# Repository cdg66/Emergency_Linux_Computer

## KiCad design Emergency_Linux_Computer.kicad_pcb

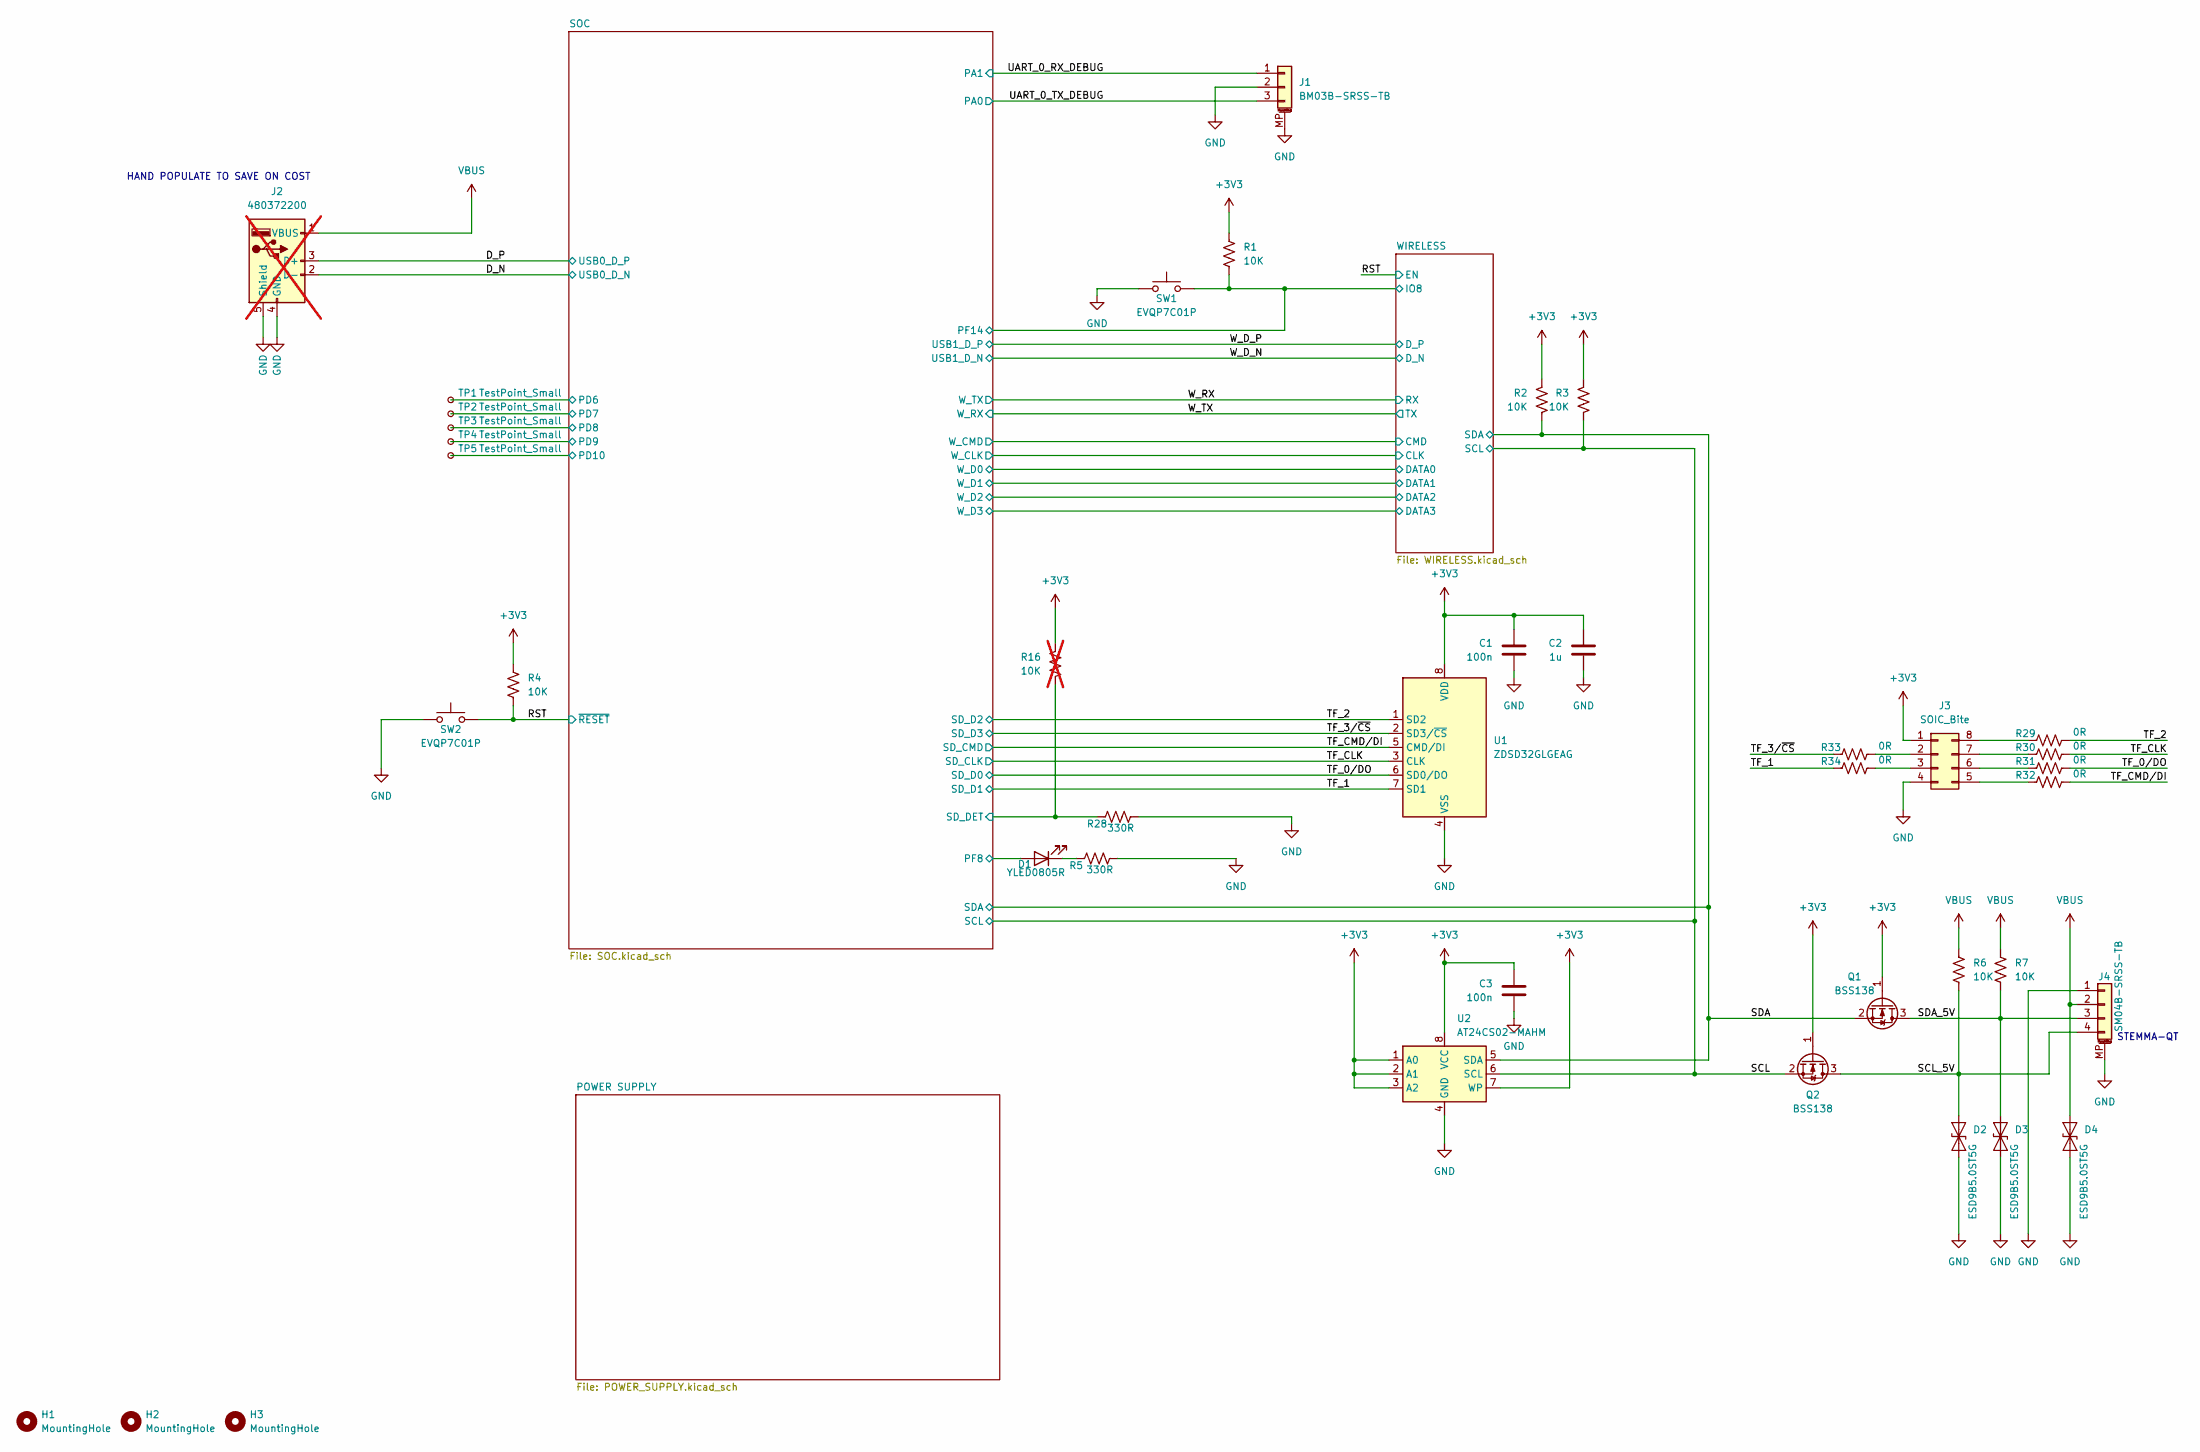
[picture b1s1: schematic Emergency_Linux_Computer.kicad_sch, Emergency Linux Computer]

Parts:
C1, C3: 100n; C_0201_0603Metric
C2: 1u; C_0603_1608Metric
D1: YLED0805R; LED_0805_2012Metric
D2, D3, D4: ESD9B5.0ST5G; D_SOD-923
H1, H2, H3: MountingHole; MountingHole_2.2mm_M2
J1: BM03B-SRSS-TB; JST_SH_BM03B-SRSS-TB_1x03-1MP_P1.00mm_Vertical
J2: 480372200; USB_A_Molex_48037-2200_Horizontal; not fitted
J3: SOIC_Bite; SOIC_clipProgSmall
J4: SM04B-SRSS-TB; JST_SH_SM04B-SRSS-TB_1x04-1MP_P1.00mm_Horizontal
Q1, Q2: BSS138; SOT-23
R1, R2, R3, R4, R6, R7: 10K; R_0201_0603Metric
R5, R28: 330R; R_0805_2012Metric
R16: 10K; R_0805_2012Metric; not fitted
R29, R30, R31, R32, R33, R34: 0R; R_0201_0603Metric
SW1, SW2: EVQP7C01P; SW_SPST_EVQP7C
TP1, TP2, TP3, TP4, TP5: TestPoint_Small; TestPoint_Pad_D1.0mm
U1: ZDSD32GLGEAG; LGA-8_8x6mm_P1.27mm
U2: AT24CS02-MAHM; DFN-8-1EP_3x2mm_P0.5mm_EP1.3x1.5mm

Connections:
+3V3: C1.1, C2.1, C3.1, J3.1, Q1.1 (G), Q2.1 (G), R1.1, R2.1, R3.1, R4.1, R16.1, U1.8 (VDD), U2.1 (A0), U2.2 (A1), U2.3 (A2), U2.7 (WP), U2.8 (VCC); also elsewhere on the board
/D_N: J2.2 (D-); also elsewhere on the board
/D_P: J2.3 (D+); also elsewhere on the board
/PF8: D1.2 (A)
/RST: R4.2, SW2.2; also elsewhere on the board
/SCL: Q2.2 (S), R3.2, U2.6 (SCL); also elsewhere on the board
/SCL_5V: D2.1 (A1), J4.4, Q2.3 (D), R6.2
/SDA: Q1.2 (S), R2.2, U2.5 (SDA); also elsewhere on the board
/SDA_5V: D3.1 (A1), J4.3, Q1.3 (D), R7.2
/SOC/PD6: TP1.1; also elsewhere on the board
/SOC/PD7: TP2.1; also elsewhere on the board
/SOC/PD8: TP3.1; also elsewhere on the board
/SOC/PD9: TP4.1; also elsewhere on the board
/SOC/PD10: TP5.1; also elsewhere on the board
/SOC/SD_DET: R16.2, R28.1; also elsewhere on the board
/TF_0/DO: R31.2, U1.6 (SD0/DO); also elsewhere on the board
/TF_1: R34.1, U1.7 (SD1); also elsewhere on the board
/TF_2: R29.2, U1.1 (SD2); also elsewhere on the board
/TF_3/~CS: R33.1, U1.2 (SD3/~CS); also elsewhere on the board
/TF_CLK: R30.2, U1.3 (CLK); also elsewhere on the board
/TF_CMD/DI: R32.2, U1.5 (CMD/DI); also elsewhere on the board
/UART_0_RX_DEBUG: J1.1; also elsewhere on the board
/UART_0_TX_DEBUG: J1.3; also elsewhere on the board
/WIRELESS/IO8: R1.2, SW1.2; also elsewhere on the board
GND: C1.2, C2.2, C3.2, D2.2 (A2), D3.2 (A2), D4.2 (A2), J1.2, J1.MP (MountPin), J2.4 (GND), J2.5 (Shield), J3.4, J4.1, J4.MP (MountPin), R5.2, R28.2, SW1.1, SW2.1, U1.4 (VSS), U2.4 (GND), U2.9 (GND); also elsewhere on the board
unnamed: D1.1 (K), R5.1
unnamed: J3.2, R33.2
unnamed: J3.3, R34.2
unnamed: J3.5, R32.1
unnamed: J3.6, R31.1
unnamed: J3.7, R30.1
unnamed: J3.8, R29.1
VBUS: D4.1 (A1), J2.1 (VBUS), J4.2, R6.1, R7.1; also elsewhere on the board

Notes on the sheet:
STEMMA-QT
HAND POPULATE TO SAVE ON COST

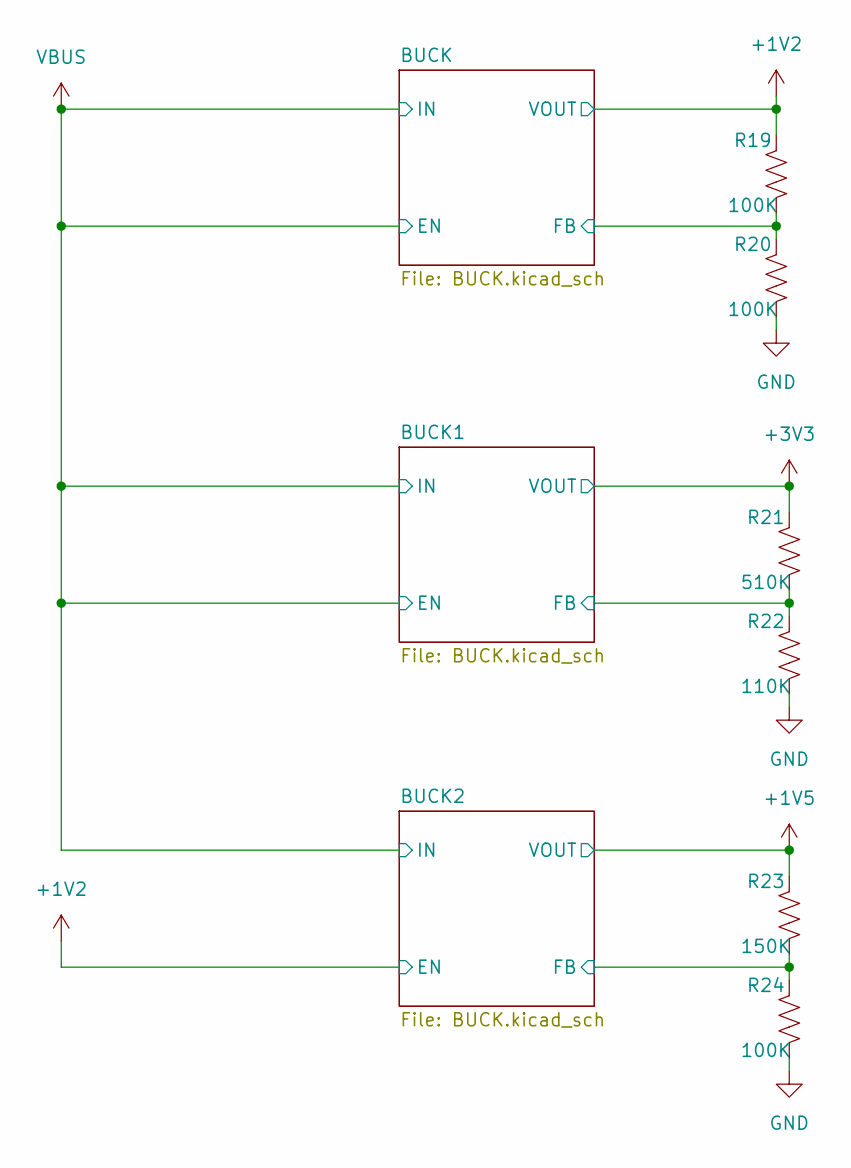
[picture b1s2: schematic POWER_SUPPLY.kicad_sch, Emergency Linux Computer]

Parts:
R19, R20, R24: 100K; R_0201_0603Metric
R21: 510K; R_0201_0603Metric
R22: 110K; R_0201_0603Metric
R23: 150K; R_0201_0603Metric

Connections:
+1V2: R19.1; also elsewhere on the board
+1V5: R23.1; also elsewhere on the board
+3V3: R21.1; also elsewhere on the board
/POWER SUPPLY/BUCK1/FB: R21.2, R22.1; also elsewhere on the board
/POWER SUPPLY/BUCK2/FB: R23.2, R24.1; also elsewhere on the board
/POWER SUPPLY/BUCK/FB: R19.2, R20.1; also elsewhere on the board
GND: R20.2, R22.2, R24.2; also elsewhere on the board

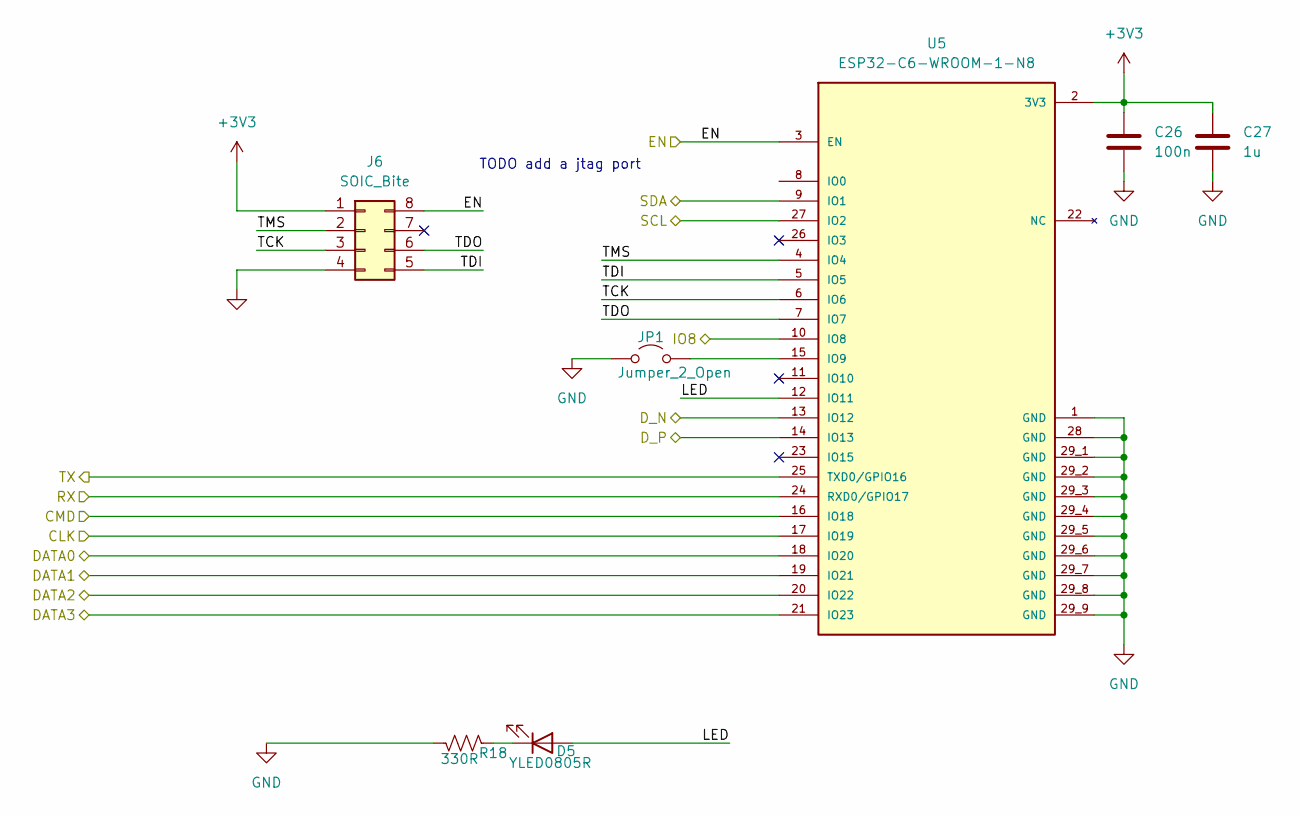
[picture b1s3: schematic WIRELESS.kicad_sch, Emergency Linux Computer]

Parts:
C26: 100n; C_0201_0603Metric
C27: 1u; C_0603_1608Metric
D5: YLED0805R; LED_0805_2012Metric
J6: SOIC_Bite; SOIC_clipProgSmall
JP1: Jumper_2_Open; SolderJumper-2_P1.3mm_Open_Pad1.0x1.5mm
R18: 330R; R_0805_2012Metric
U5: ESP32-C6-WROOM-1-N8; XCVR_ESP32-C6-WROOM-1-N8; PARTREV 1.0

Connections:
+3V3: C26.1, C27.1, J6.1, U5.2 (3V3); also elsewhere on the board
/RST: J6.8, U5.3 (EN); also elsewhere on the board
/SCL: U5.27 (IO2); also elsewhere on the board
/SDA: U5.9 (IO1); also elsewhere on the board
/SOC/W_CLK: U5.17 (IO19); also elsewhere on the board
/SOC/W_CMD: U5.16 (IO18); also elsewhere on the board
/SOC/W_D0: U5.18 (IO20); also elsewhere on the board
/SOC/W_D1: U5.19 (IO21); also elsewhere on the board
/SOC/W_D2: U5.20 (IO22); also elsewhere on the board
/SOC/W_D3: U5.21 (IO23); also elsewhere on the board
/WIRELESS/IO8: U5.10 (IO8); also elsewhere on the board
/WIRELESS/LED: D5.2 (A), U5.12 (IO11)
/WIRELESS/TCK: J6.3, U5.6 (IO6)
/WIRELESS/TDI: J6.5, U5.5 (IO5)
/WIRELESS/TDO: J6.6, U5.7 (IO7)
/WIRELESS/TMS: J6.2, U5.4 (IO4)
/W_D_N: U5.13 (IO12); also elsewhere on the board
/W_D_P: U5.14 (IO13); also elsewhere on the board
/W_RX: U5.24 (RXD0/GPIO17); also elsewhere on the board
/W_TX: U5.25 (TXD0/GPIO16); also elsewhere on the board
GND: C26.2, C27.2, J6.4, JP1.1 (A), R18.2, U5.1 (GND), U5.28 (GND), U5.29_1 (GND), U5.29_2 (GND), U5.29_3 (GND), U5.29_4 (GND), U5.29_5 (GND), U5.29_6 (GND), U5.29_7 (GND), U5.29_8 (GND), U5.29_9 (GND); also elsewhere on the board
unnamed: D5.1 (K), R18.1
unnamed: JP1.2 (B), U5.15 (IO9)

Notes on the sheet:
TODO add a jtag port

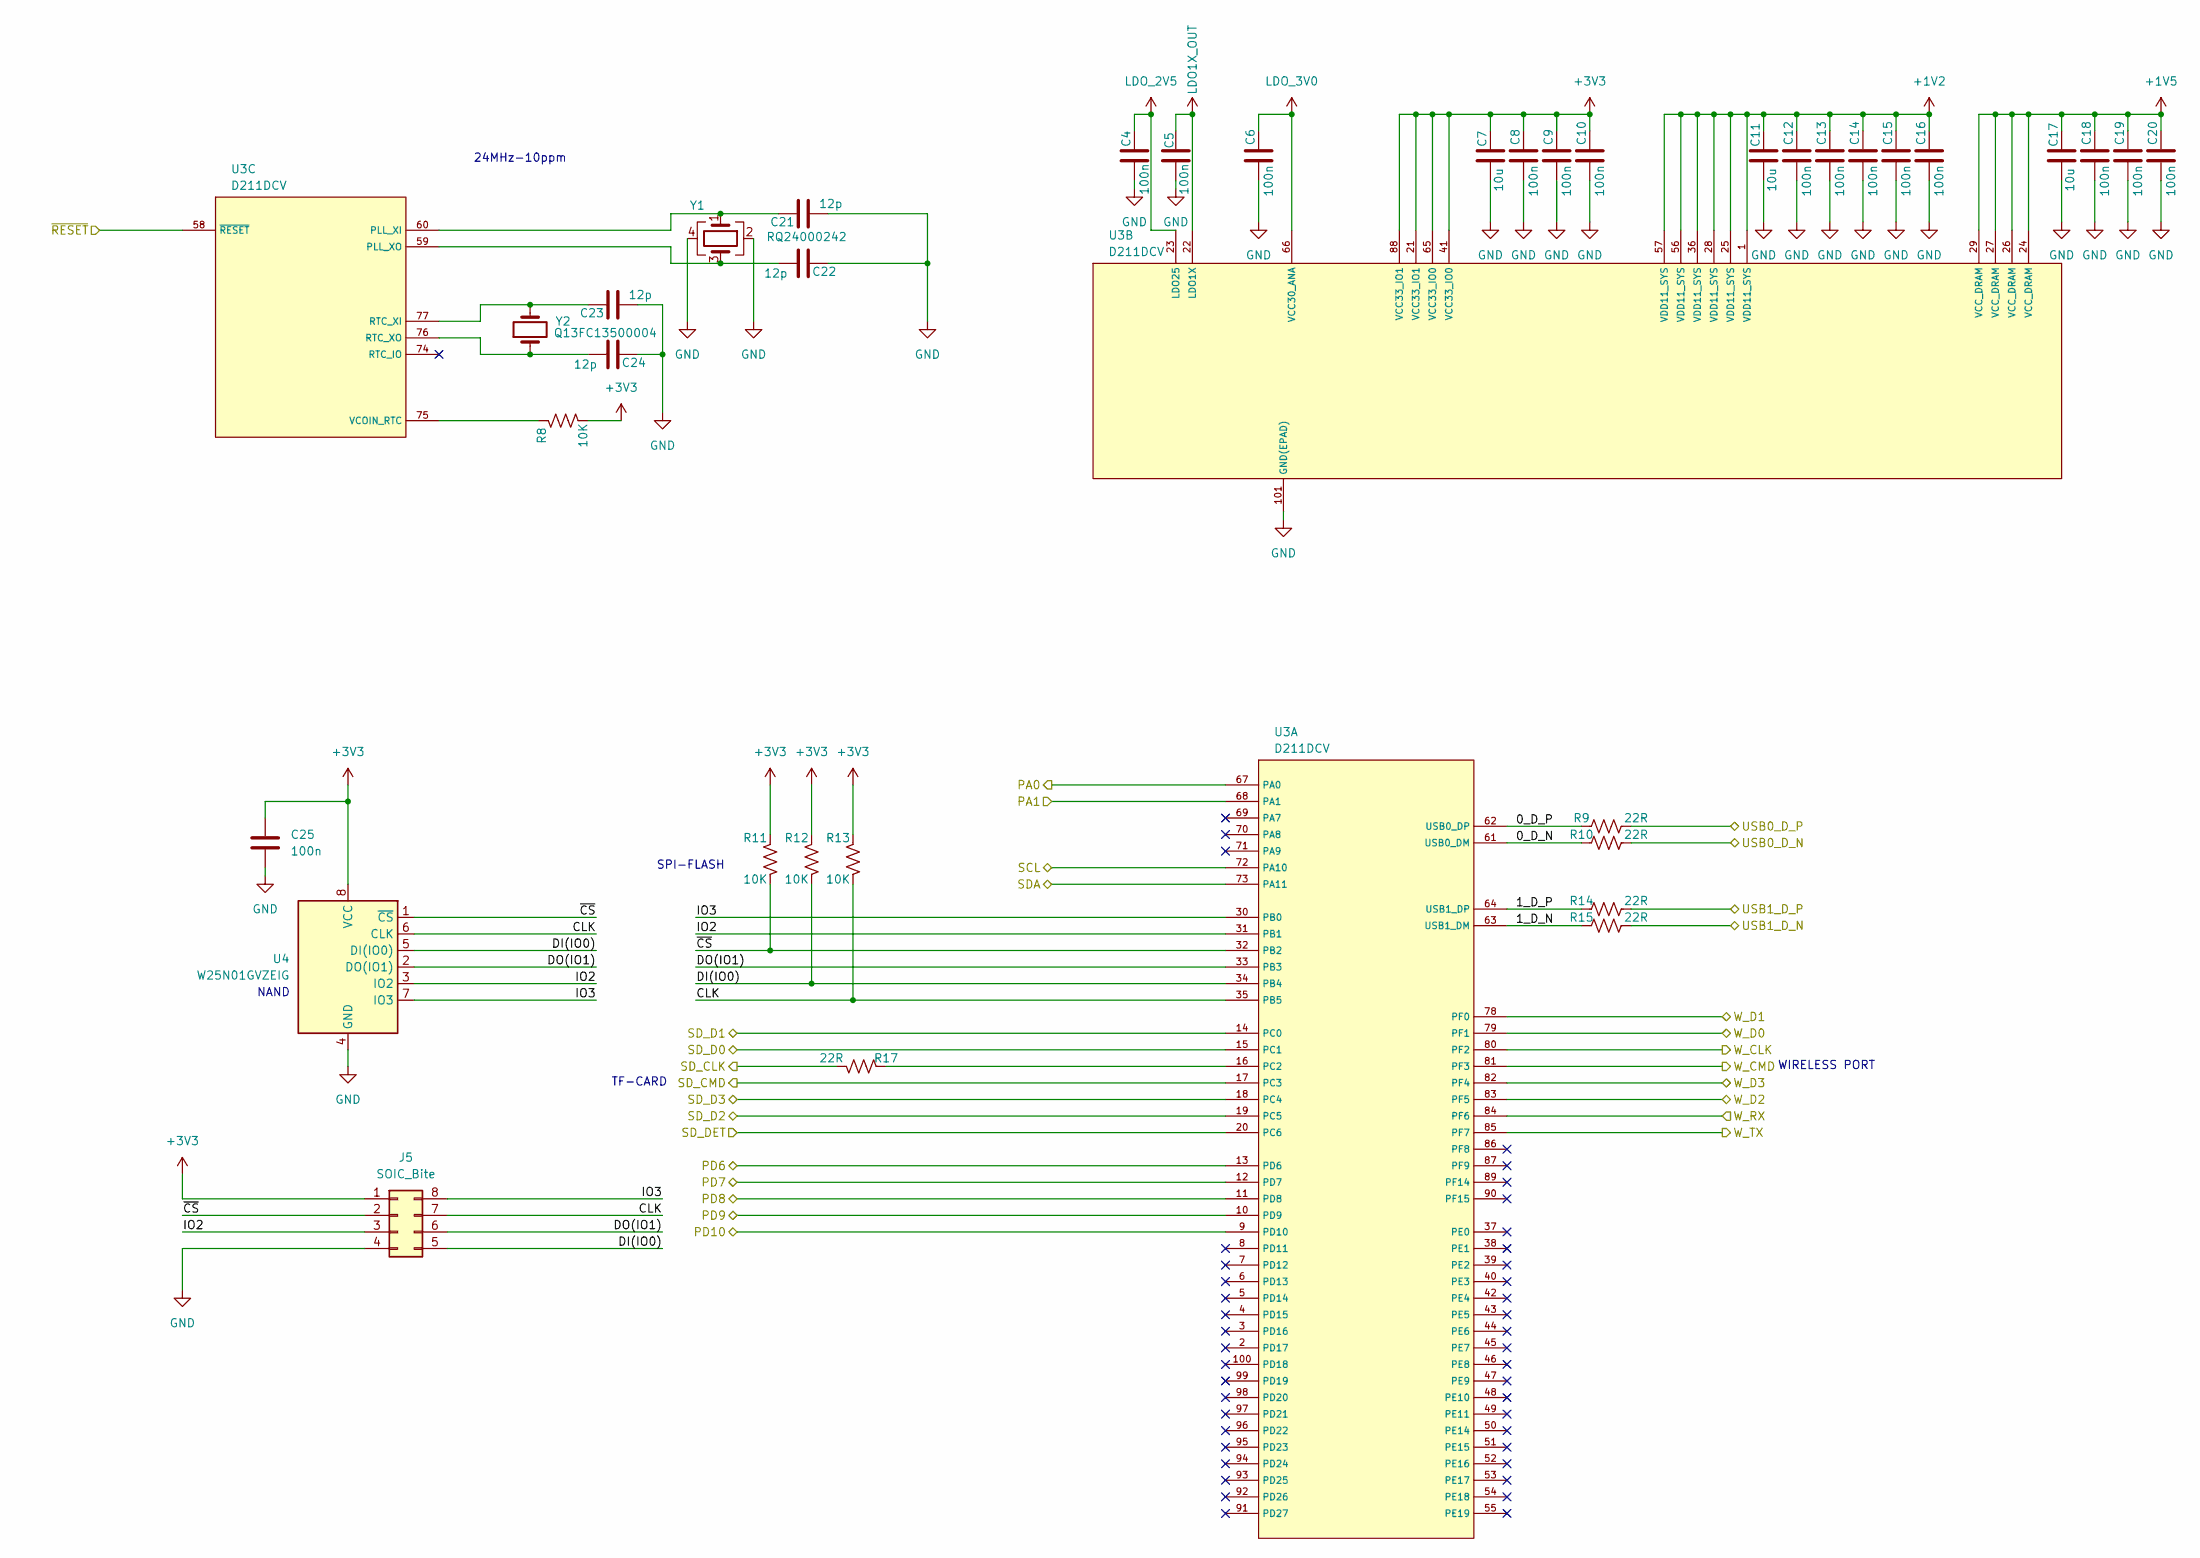
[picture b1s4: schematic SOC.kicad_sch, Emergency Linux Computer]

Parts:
C4, C5, C6, C8, C9, C10, C12, C13, C14, C15, C16, C18, C19, C20, C25: 100n; C_0201_0603Metric
C7, C11, C17: 10u; C_0603_1608Metric
C21, C22, C23, C24: 12p; C_0201_0603Metric
J5: SOIC_Bite; SOIC_clipProgSmall
R8, R11, R12, R13: 10K; R_0201_0603Metric
R9, R10, R14, R15, R17: 22R; R_0201_0603Metric
U3: D211DCV; ArtInChip_QFN-100-1EP_12x12mm_P0.4mm_EP7.4x7.4mm
U4: W25N01GVZEIG; WSON-8-1EP_8x6mm_P1.27mm_EP3.4x4.3mm
Y1: RQ24000242; Crystal_SMD_2520-4Pin_2.5x2.0mm
Y2: Q13FC13500004; Crystal_SMD_3215-2Pin_3.2x1.5mm

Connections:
+1V2: C11.1, C12.1, C13.1, C14.1, C15.1, C16.1, U3.1 (VDD11_SYS), U3.25 (VDD11_SYS), U3.28 (VDD11_SYS), U3.36 (VDD11_SYS), U3.56 (VDD11_SYS), U3.57 (VDD11_SYS); also elsewhere on the board
+1V5: C17.1, C18.1, C19.1, C20.1, U3.24 (VCC_DRAM), U3.26 (VCC_DRAM), U3.27 (VCC_DRAM), U3.29 (VCC_DRAM); also elsewhere on the board
+3V3: C7.1, C8.1, C9.1, C10.1, C25.1, J5.1, R8.2, R11.1, R12.1, R13.1, U3.21 (VCC33_IO1), U3.41 (VCC33_IO0), U3.65 (VCC33_IO0), U3.88 (VCC33_IO1), U4.8 (VCC); also elsewhere on the board
/D_N: R10.2; also elsewhere on the board
/D_P: R9.2; also elsewhere on the board
/RST: U3.58 (~RESET); also elsewhere on the board
/SCL: U3.72 (PA10); also elsewhere on the board
/SDA: U3.73 (PA11); also elsewhere on the board
/SOC/0_D_N: R10.1, U3.61 (USB0_DM)
/SOC/0_D_P: R9.1, U3.62 (USB0_DP)
/SOC/1_D_N: R15.1, U3.63 (USB1_DM)
/SOC/1_D_P: R14.1, U3.64 (USB1_DP)
/SOC/CLK: J5.7, R13.2, U3.35 (PB5), U4.6 (CLK)
/SOC/DI(IO0): J5.5, R12.2, U3.34 (PB4), U4.5 (DI(IO0))
/SOC/DO(IO1): J5.6, U3.33 (PB3), U4.2 (DO(IO1))
/SOC/IO2: J5.3, U3.31 (PB1), U4.3 (IO2)
/SOC/IO3: J5.8, U3.30 (PB0), U4.7 (IO3)
/SOC/PD6: U3.13 (PD6); also elsewhere on the board
/SOC/PD7: U3.12 (PD7); also elsewhere on the board
/SOC/PD8: U3.11 (PD8); also elsewhere on the board
/SOC/PD9: U3.10 (PD9); also elsewhere on the board
/SOC/PD10: U3.9 (PD10); also elsewhere on the board
/SOC/SD_DET: U3.20 (PC6); also elsewhere on the board
/SOC/W_CLK: U3.80 (PF2); also elsewhere on the board
/SOC/W_CMD: U3.81 (PF3); also elsewhere on the board
/SOC/W_D0: U3.79 (PF1); also elsewhere on the board
/SOC/W_D1: U3.78 (PF0); also elsewhere on the board
/SOC/W_D2: U3.83 (PF5); also elsewhere on the board
/SOC/W_D3: U3.82 (PF4); also elsewhere on the board
/SOC/~CS: J5.2, R11.2, U3.32 (PB2), U4.1 (~CS)
/TF_0/DO: U3.15 (PC1); also elsewhere on the board
/TF_1: U3.14 (PC0); also elsewhere on the board
/TF_2: U3.19 (PC5); also elsewhere on the board
/TF_3/~CS: U3.18 (PC4); also elsewhere on the board
/TF_CLK: R17.2; also elsewhere on the board
/TF_CMD/DI: U3.17 (PC3); also elsewhere on the board
/UART_0_RX_DEBUG: U3.68 (PA1); also elsewhere on the board
/UART_0_TX_DEBUG: U3.67 (PA0); also elsewhere on the board
/W_D_N: R15.2; also elsewhere on the board
/W_D_P: R14.2; also elsewhere on the board
/W_RX: U3.85 (PF7); also elsewhere on the board
/W_TX: U3.84 (PF6); also elsewhere on the board
GND: C4.2, C5.2, C6.2, C7.2, C8.2, C9.2, C10.2, C11.2, C12.2, C13.2, C14.2, C15.2, C16.2, C17.2, C18.2, C19.2, C20.2, C21.2, C22.1, C23.2, C24.1, C25.2, J5.4, U3.101 (GND(EPAD)), U4.4 (GND), U4.9 (GND), Y1.2, Y1.4; also elsewhere on the board
LDO1X_OUT: C5.1, U3.22 (LDO1X)
LDO_2V5: C4.1, U3.23 (LDO25)
LDO_3V0: C6.1, U3.66 (VCC30_ANA)
unnamed: R17.1, U3.16 (PC2)
unnamed: C21.1, U3.60 (PLL_XI), Y1.1
unnamed: C22.2, U3.59 (PLL_XO), Y1.3
unnamed: C23.1, U3.77 (RTC_XI), Y2.2
unnamed: C24.2, U3.76 (RTC_XO), Y2.1
unnamed: R8.1, U3.75 (VCOIN_RTC)

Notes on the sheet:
24MHz-10ppm
SPI-FLASH
WIRELESS PORT
NAND
TF-CARD

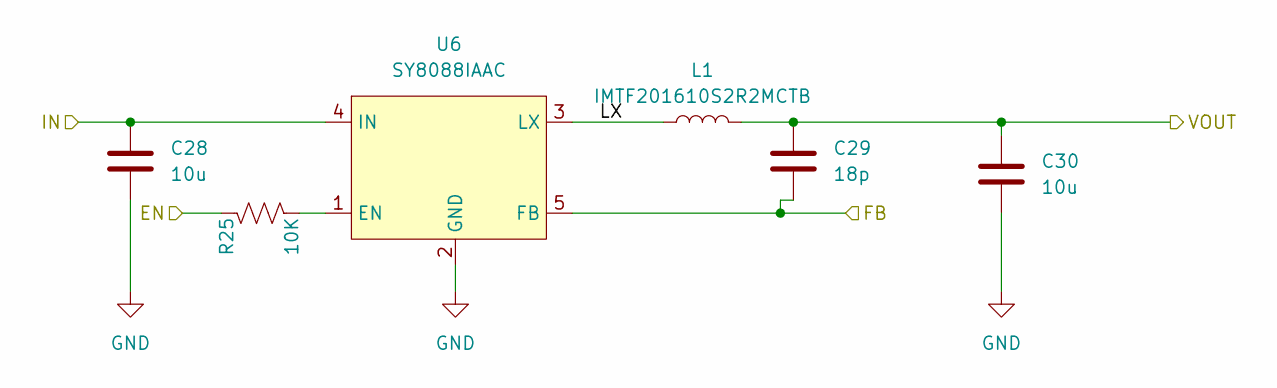
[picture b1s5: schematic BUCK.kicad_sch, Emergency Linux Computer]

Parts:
C28, C30: 10u; C_0603_1608Metric
C29: 18p; C_0201_0603Metric
L1: IMTF201610S2R2MCTB; L_Murata_DFE201610P
R25: 10K; R_0201_0603Metric
U6: SY8088IAAC; SOT-23-5

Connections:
+1V2: C29.1, C30.1, L1.2; also elsewhere on the board
/POWER SUPPLY/BUCK/FB: C29.2, U6.5 (FB); also elsewhere on the board
/POWER SUPPLY/BUCK/LX: L1.1, U6.3 (LX)
GND: C28.2, C30.2, U6.2 (GND); also elsewhere on the board
unnamed: R25.2, U6.1 (EN)
VBUS: C28.1, R25.1, U6.4 (IN); also elsewhere on the board

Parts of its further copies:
C31, C33, C34, C36: 10u; C_0603_1608Metric
C32, C35: 18p; C_0201_0603Metric
L2, L3: IMTF201610S2R2MCTB; L_Murata_DFE201610P
R26, R27: 10K; R_0201_0603Metric
U7, U8: SY8088IAAC; SOT-23-5

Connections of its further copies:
+1V2: R27.1; also elsewhere on the board
+1V5: C35.1, C36.1, L3.2; also elsewhere on the board
+3V3: C32.1, C33.1, L2.2; also elsewhere on the board
/POWER SUPPLY/BUCK1/FB: C32.2, U7.5 (FB); also elsewhere on the board
/POWER SUPPLY/BUCK1/LX: L2.1, U7.3 (LX)
/POWER SUPPLY/BUCK2/FB: C35.2, U8.5 (FB); also elsewhere on the board
/POWER SUPPLY/BUCK2/LX: L3.1, U8.3 (LX)
GND: C31.2, C33.2, C34.2, C36.2, U7.2 (GND), U8.2 (GND); also elsewhere on the board
unnamed: R26.2, U7.1 (EN)
unnamed: R27.2, U8.1 (EN)
VBUS: C31.1, C34.1, R26.1, U7.4 (IN), U8.4 (IN); also elsewhere on the board

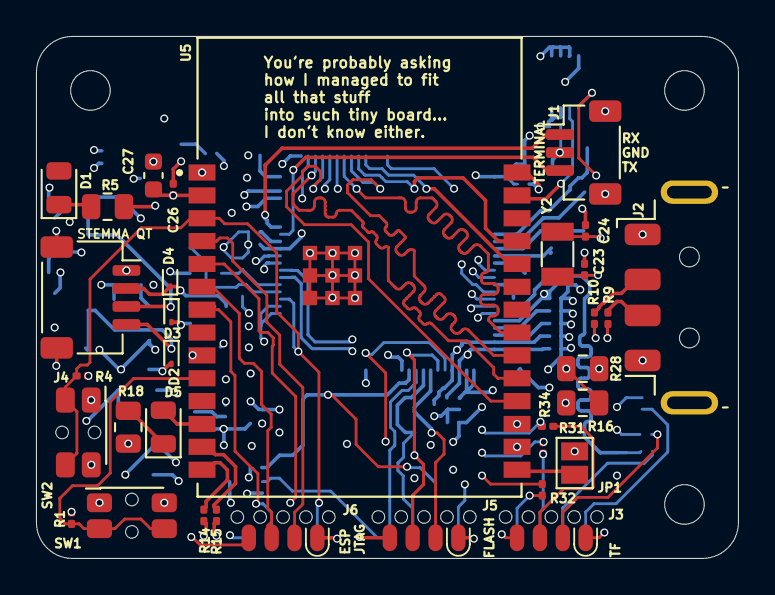
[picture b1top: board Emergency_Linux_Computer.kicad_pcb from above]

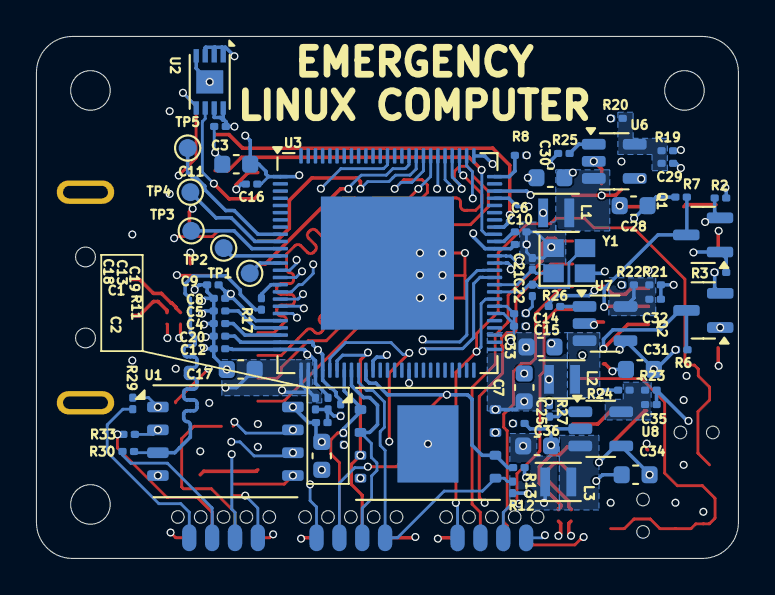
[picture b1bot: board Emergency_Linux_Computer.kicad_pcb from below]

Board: 8 copper layers, 39.0 x 29.0 mm, 107 parts (71 on the bottom side), 79 nets.

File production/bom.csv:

Designator,Footprint,Quantity,Value,LCSC Part #
"C1, C10, C12, C13, C14, C15, C16, C18, C19, C20, C25, C26, C3, C4, C5, C6, C8, C9",0201,18,100n,
"C11, C17, C28, C30, C31, C33, C34, C36, C7",0603,9,10u,
"C2, C27",0603,2,1u,
"C21, C22, C23, C24",0201,4,12p,
"C29, C32, C35",0201,3,18p,
"D1, D5",0805,2,YLED0805R,
"D2, D3, D4",D_SOD-923,3,ESD9B5.0ST5G,
J1,JST_SH_BM03B-SRSS-TB_1x03-1MP_P1.00mm_Vertical,1,BM03B-SRSS-TB,
"J3, J5, J6",SOIC_clipProgSmall,3,SOIC_Bite,
J4,JST_SH_SM04B-SRSS-TB_1x04-1MP_P1.00mm_Horizontal,1,SM04B-SRSS-TB,
JP1,SolderJumper-2_P1.3mm_Open_Pad1.0x1.5mm,1,Jumper_2_Open,
"L1, L2, L3",L_Murata_DFE201610P,3,IMTF201610S2R2MCTB,
"Q1, Q2",SOT-23,2,BSS138,
"R1, R11, R12, R13, R2, R25, R26, R27, R3, R4, R6, R7, R8",0201,13,10K,
"R10, R14, R15, R17, R9",0201,5,22R,
"R18, R28, R5",0805,3,330R,
"R19, R20, R24",0201,3,100K,
R21,0201,1,510K,
R22,0201,1,110K,
R23,0201,1,150K,
"R29, R30, R31, R32, R33, R34",0201,6,0R,
"SW1, SW2",SW_SPST_EVQP7C,2,EVQP7C01P,
U1,LGA-8_8x6mm_P1.27mm,1,ZDSD32GLGEAG,
U2,DFN-8-1EP_3x2mm_P0.5mm_EP1.3x1.5mm,1,AT24CS02-MAHM,
U3,ArtInChip_QFN-100-1EP_12x12mm_P0.4mm_EP7.4x7.4mm,1,D211DCV,
U4,WSON-8-1EP_8x6mm_P1.27mm_EP3.4x4.3mm,1,W25Q128JVE,
U5,XCVR_ESP32-C6-WROOM-1-N8,1,ESP32-C6-WROOM-1-N8,
"U6, U7, U8",SOT-23-5,3,SY8088IAAC,
Y1,Crystal_SMD_2520-4Pin_2.5x2.0mm,1,RQ24000242,
Y2,Crystal_SMD_3215-2Pin_3.2x1.5mm,1,Q13FC13500004,

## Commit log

2024-12-20 Version B
2024-12-20 rev B
